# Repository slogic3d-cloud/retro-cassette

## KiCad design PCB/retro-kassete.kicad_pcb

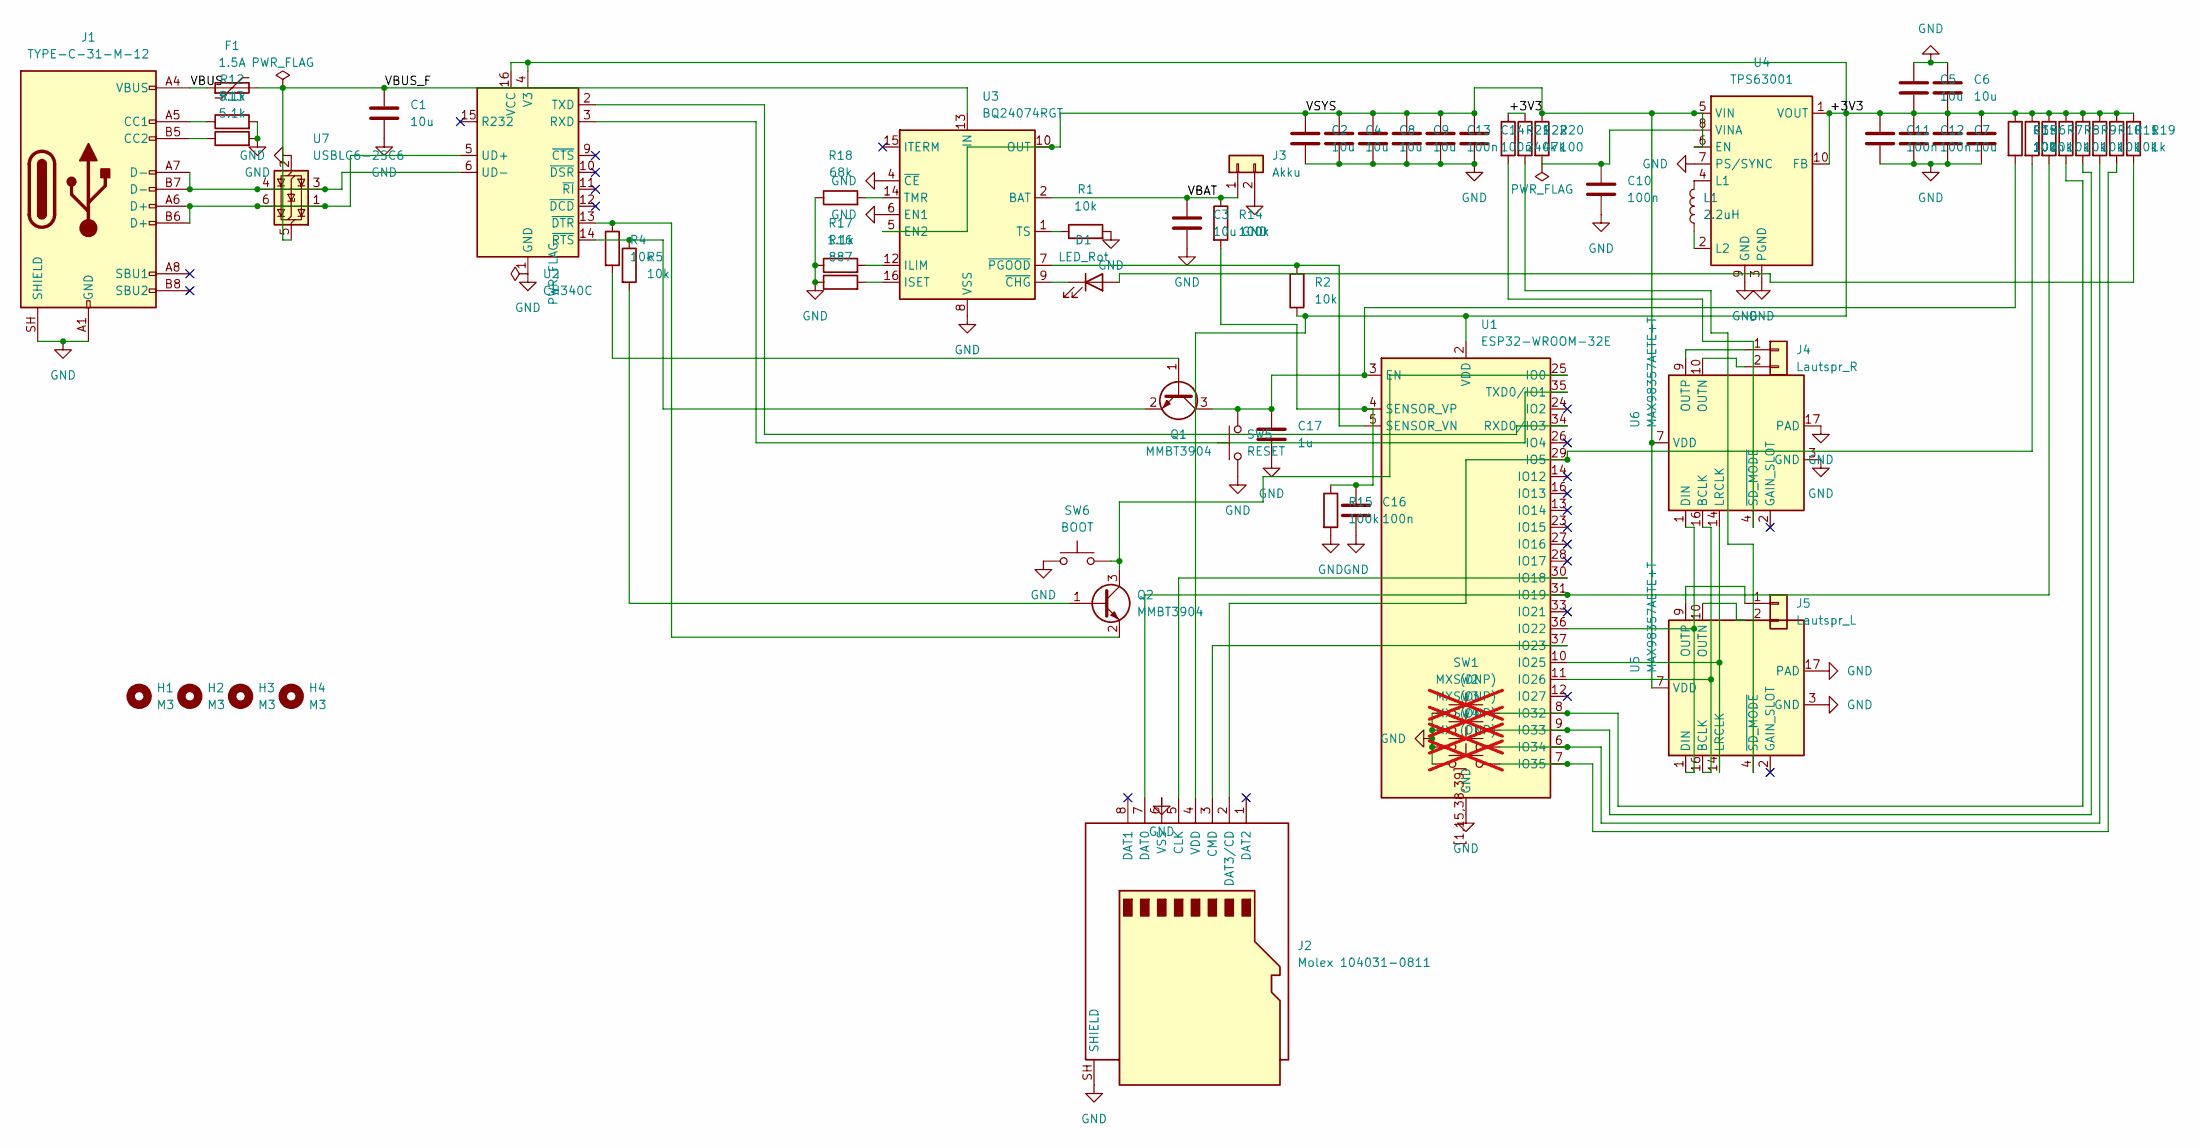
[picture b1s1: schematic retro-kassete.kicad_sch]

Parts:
C1, C2, C3: 10u; C_0805_2012Metric; LCSC C15850
C4, C5, C6, C7, C8, C9: 10u; C_0603_1608Metric; LCSC C19702
C10, C11, C12, C13, C14, C15, C16: 100n; C_0402_1005Metric; LCSC C1525
C17: 1u; C_0402_1005Metric; LCSC C52923
D1: LED_Rot; LED_0603_1608Metric; LCSC C2286
F1: 1.5A; Fuse_1206_3216Metric; LCSC C135341
H1, H2, H3, H4: M3; MountingHole_3.2mm_M3
J1: TYPE-C-31-M-12; USB_C_Receptacle_HRO_TYPE-C-31-M-12; LCSC C165948
J2: Molex 104031-0811; microSD_HC_Molex_104031-0811; LCSC C585350
J3: Akku; JST_PH_S2B-PH-SM4-TB_1x02-1MP_P2.00mm_Horizontal; LCSC C295747
J4: Lautspr_R; JST_PH_S2B-PH-SM4-TB_1x02-1MP_P2.00mm_Horizontal; LCSC C295747
J5: Lautspr_L; JST_PH_S2B-PH-SM4-TB_1x02-1MP_P2.00mm_Horizontal; LCSC C295747
L1: 2.2uH; L_Sunlord_SWPA4012S; LCSC C96870
Q1, Q2: MMBT3904; SOT-23; LCSC C20526
R1, R2, R3, R4, R5, R6, R7, R8, R9, R10, R11: 10k; R_0402_1005Metric; LCSC C25744
R12, R13: 5.1k; R_0402_1005Metric; LCSC C25905
R14, R15: 100k; R_0402_1005Metric; LCSC C25741
R16: 887; R_0402_1005Metric; LCSC C4012675
R17: 1.1k; R_0402_1005Metric; LCSC C25860
R18: 68k; R_0402_1005Metric; LCSC C36871
R19: 1k; R_0402_1005Metric; LCSC C11702
R20: 100; R_0402_1005Metric; LCSC C25076
R21: 240k; R_0402_1005Metric; LCSC C138029
R22: 47k; R_0402_1005Metric; LCSC C25792
SW1, SW2, SW3, SW4: MX (DNP); SW_Cherry_MX_1.00u_PCB; not fitted
SW5: RESET; SW_Push_1P1T_XKB_TS-1187A; LCSC C318884
SW6: BOOT; SW_Push_1P1T_XKB_TS-1187A; LCSC C318884
U1: ESP32-WROOM-32E; LCSC C701342
U2: CH340C; SOIC-16_3.9x9.9mm_P1.27mm; LCSC C84681
U3: BQ24074RGT; VQFN-16-1EP_3x3mm_P0.5mm_EP1.6x1.6mm; LCSC C54313
U4: TPS63001; Texas_DRC0010J_ThermalVias; LCSC C28060
U5, U6: MAX98357AETE+T; TQFN-16-1EP_3x3mm_P0.5mm_EP1.23x1.23mm; LCSC C910544
U7: USBLC6-2SC6; SOT-23-6; LCSC C2687116

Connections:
/+3V3: C5.2, C6.2, C7.1, C11.1, C12.1, C15.1, J2.4 (VDD), R2.1, R3.1, R6.1, R7.1, R8.1, R9.1, R10.1, R11.1, R19.1, R21.1, R22.1, U1.2 (VDD), U2.4 (V3), U2.16 (VCC), U4.1 (VOUT), U4.10 (FB)
/VBAT: C3.1, J3.1, R14.1, U3.2 (BAT), U3.3 (BAT)
/VBUS: F1.1, J1.A4 (VBUS), J1.A9 (VBUS), J1.B4 (VBUS), J1.B9 (VBUS)
/VBUS_F: C1.1, F1.2, U3.13 (IN), U7.5 (VBUS)
/VSYS: C2.1, C4.1, C8.1, C9.1, C13.1, C14.1, R20.1, U3.5 (EN2), U3.10 (OUT), U3.11 (OUT), U4.5 (VIN), U4.6 (EN), U5.7 (VDD), U5.8 (VDD), U6.7 (VDD), U6.8 (VDD)
GND: C1.2, C2.2, C3.2, C4.2, C5.1, C6.1, C7.2, C8.2, C9.2, C10.2, C11.2, C12.2, C13.2, C14.2, C15.2, C16.2, C17.1, J1.A1 (GND), J1.A12 (GND), J1.B1 (GND), J1.B12 (GND), J1.SH (SHIELD), J2.6 (VSS), J2.SH (SHIELD), J3.2, R1.2, R12.2, R13.2, R15.2, R16.1, R17.1, R18.1, SW1.1, SW2.1, SW3.1, SW4.1, SW5.1, SW6.1, U1.1 (GND), U1.15 (GND), U1.38 (GND), U1.39 (GND), U1.[1,15,38,39] (GND), U2.1 (GND), U3.4 (~CE), U3.6 (EN1), U3.8 (VSS), U3.17 (VSS), U4.3 (PGND), U4.7 (PS/SYNC), U4.9 (GND), U4.11 (PGND), U5.3 (GND), U5.11 (GND), U5.15 (GND), U5.17 (PAD), U6.3 (GND), U6.11 (GND), U6.15 (GND), U6.17 (PAD), U7.2 (GND)
unnamed: D1.2 (A), R19.2
unnamed: D1.1 (K), U3.9 (~CHG)
unnamed: J1.A5 (CC1), R12.1
unnamed: J1.B5 (CC2), R13.1
unnamed: J2.5 (CLK), U1.30 (IO18)
unnamed: J2.3 (CMD), U1.37 (IO23)
unnamed: J2.7 (DAT0), R7.2, U1.31 (IO19)
unnamed: J2.2 (DAT3/CD), R6.2, U1.29 (IO5)
unnamed: J4.1, U6.9 (OUTP)
unnamed: J4.2, U6.10 (OUTN)
unnamed: J5.1, U5.9 (OUTP)
unnamed: J5.2, U5.6 (NC), U5.10 (OUTN)
unnamed: Q1.1 (B), R4.2
unnamed: C17.2, Q1.3 (C), R3.2, SW5.2, U1.3 (EN)
unnamed: Q1.2 (E), R5.1, U2.14 (~RTS)
unnamed: Q2.1 (B), R5.2
unnamed: Q2.3 (C), SW6.2, U1.25 (IO0)
unnamed: Q2.2 (E), R4.1, U2.13 (~DTR)
unnamed: U1.36 (IO22), U5.1 (DIN), U6.1 (DIN)
unnamed: U1.10 (IO25), U5.14 (LRCLK), U6.14 (LRCLK)
unnamed: U1.11 (IO26), U5.16 (BCLK), U6.16 (BCLK)
unnamed: R8.2, SW1.2, U1.8 (IO32)
unnamed: R9.2, SW2.2, U1.9 (IO33)
unnamed: R10.2, SW3.2, U1.6 (IO34)
unnamed: R11.2, SW4.2, U1.7 (IO35)
unnamed: U1.34 (RXD0/IO3), U2.2 (TXD)
unnamed: R2.2, U1.5 (SENSOR_VN), U3.7 (~PGOOD)
unnamed: C16.1, R14.2, R15.1, U1.4 (SENSOR_VP)
unnamed: U1.35 (TXD0/IO1), U2.3 (RXD)
unnamed: J1.A6 (D+), J1.B6 (D+), U2.5 (UD+), U7.1 (I/O1), U7.6 (I/O1)
unnamed: J1.A7 (D-), J1.B7 (D-), U2.6 (UD-), U7.3 (I/O2), U7.4 (I/O2)
unnamed: R17.2, U3.12 (ILIM)
unnamed: R16.2, U3.16 (ISET)
unnamed: R18.2, U3.14 (TMR)
unnamed: R1.1, U3.1 (TS)
unnamed: L1.2, U4.4 (L1)
unnamed: L1.1, U4.2 (L2)
unnamed: C10.1, R20.2, U4.8 (VINA)
unnamed: R22.2, U5.4 (~SD_MODE)
unnamed: R21.2, U6.4 (~SD_MODE)

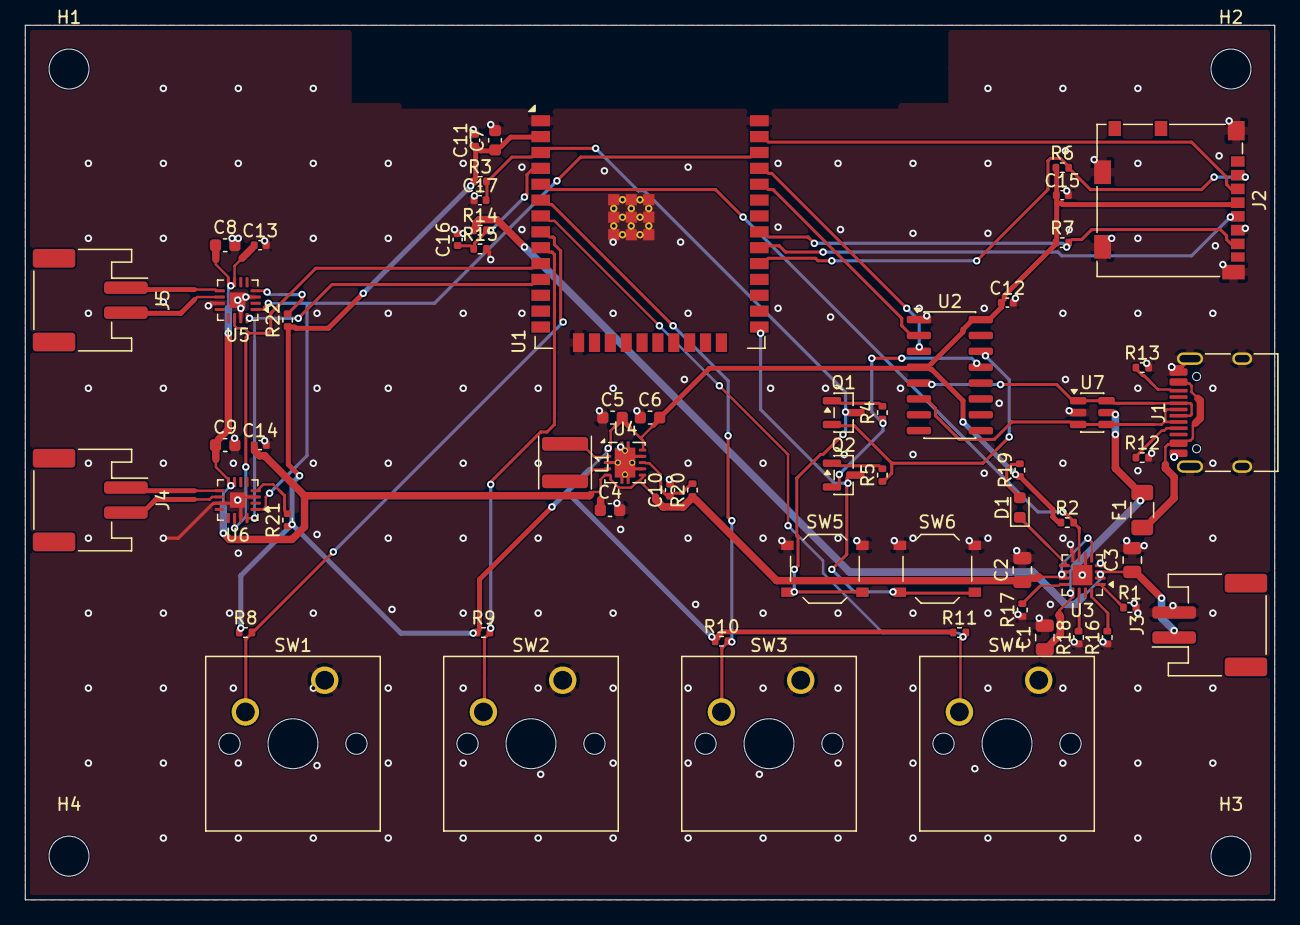
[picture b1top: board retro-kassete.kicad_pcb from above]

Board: 2 copper layers, 100.0 x 70.0 mm, 66 parts (0 on the bottom side), 46 nets.

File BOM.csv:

Ref,Teil,Wert,Footprint,Menge,LCSC,Link,Stueckpreis_USD,Versand,Notiz
U1,ESP32-WROOM-32E-N8,ESP32-WROOM-32E-N8,RF_Module:ESP32-WROOM-32E,1,C701342,https://www.lcsc.com/product-detail/C701342.html,4.5662,JLC PCBA,Extended; Modul -> JLC Standard PCBA
U2,CH340C,CH340C,Package_SO:SOIC-16_3.9x9.9mm_P1.27mm,1,C84681,https://www.lcsc.com/product-detail/C84681.html,0.5447,JLC PCBA,Extended; USB-Seriell zum Flashen
U3,BQ24074RGTR,BQ24074RGTR,Package_DFN_QFN:VQFN-16-1EP_3x3mm_P0.5mm_EP1.6x1.6mm,1,C54313,https://www.lcsc.com/product-detail/C54313.html,2.118,JLC PCBA,Extended; Lader mit Power-Path
U4,TPS63001DRCR,TPS63001DRCR,Package_SON:Texas_DRC0010J_ThermalVias,1,C28060,https://www.lcsc.com/product-detail/C28060.html,1.6126,JLC PCBA,Extended; Buck-Boost 3.3 V
U5,MAX98357AETE+T,MAX98357AETE+T,Package_DFN_QFN:TQFN-16-1EP_3x3mm_P0.5mm_EP1.23x1.23mm,1,C910544,https://www.lcsc.com/product-detail/C910544.html,1.3084,JLC PCBA,Extended; Audio links
U6,MAX98357AETE+T,MAX98357AETE+T,Package_DFN_QFN:TQFN-16-1EP_3x3mm_P0.5mm_EP1.23x1.23mm,1,C910544,https://www.lcsc.com/product-detail/C910544.html,1.3084,JLC PCBA,Extended; Audio rechts
U7,USBLC6-2SC6,USBLC6-2SC6,Package_TO_SOT_SMD:SOT-23-6,1,C2687116,https://www.lcsc.com/product-detail/C2687116.html,0.0478,JLC PCBA,Extended; ESD USB
J1,USB-C 16P,TYPE-C-31-M-12,Connector_USB:USB_C_Receptacle_HRO_TYPE-C-31-M-12,1,C165948,https://www.lcsc.com/product-detail/C165948.html,0.1868,JLC PCBA,Extended
Q1,MMBT3904,MMBT3904,Package_TO_SOT_SMD:SOT-23,1,C20526,https://www.lcsc.com/product-detail/C20526.html,0.0117,JLC PCBA,Basic; Auto-Reset
Q2,MMBT3904,MMBT3904,Package_TO_SOT_SMD:SOT-23,1,C20526,https://www.lcsc.com/product-detail/C20526.html,0.0117,JLC PCBA,Basic; Auto-Reset
